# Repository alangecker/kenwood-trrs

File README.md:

# Kenwood TRRS Adapter
A tiny board, which allows using Kenwood headsets on smartphones, including the Push-To-Talk functionality.

## Schematic

## Bill of Materials
| Qty | Ident | Part                     | Notes
|----:|------:|--------------------------|------------
|   1 |    J2 | 2.5mm Jack PJ-211A       |
|   1 |    J3 | 3.5mm Jack PJ-313        | 
|   1 |    J1 | 4-pin 3.5mm Jack Cable   | cut in half
|   1 |    Q1 | AO3400 N-Channel MOSFET  | or BSS138
|   1 |    C1 | 100uF 6.3V RM2 5.0mm Elco
|   1 | R1,R5 | Resistor 100kΩ 0805
|   1 |    R4 | Resistor 2MΩ 0805
|   2 | R2,R3 | Resistor 20Ω 0805
|   1 |       | Heat shrink tube

## License

To the extent possible under law, Andreas Langecker has waived all copyright and related or neighboring rights to kenwood-trrs. This work is published from: Germany

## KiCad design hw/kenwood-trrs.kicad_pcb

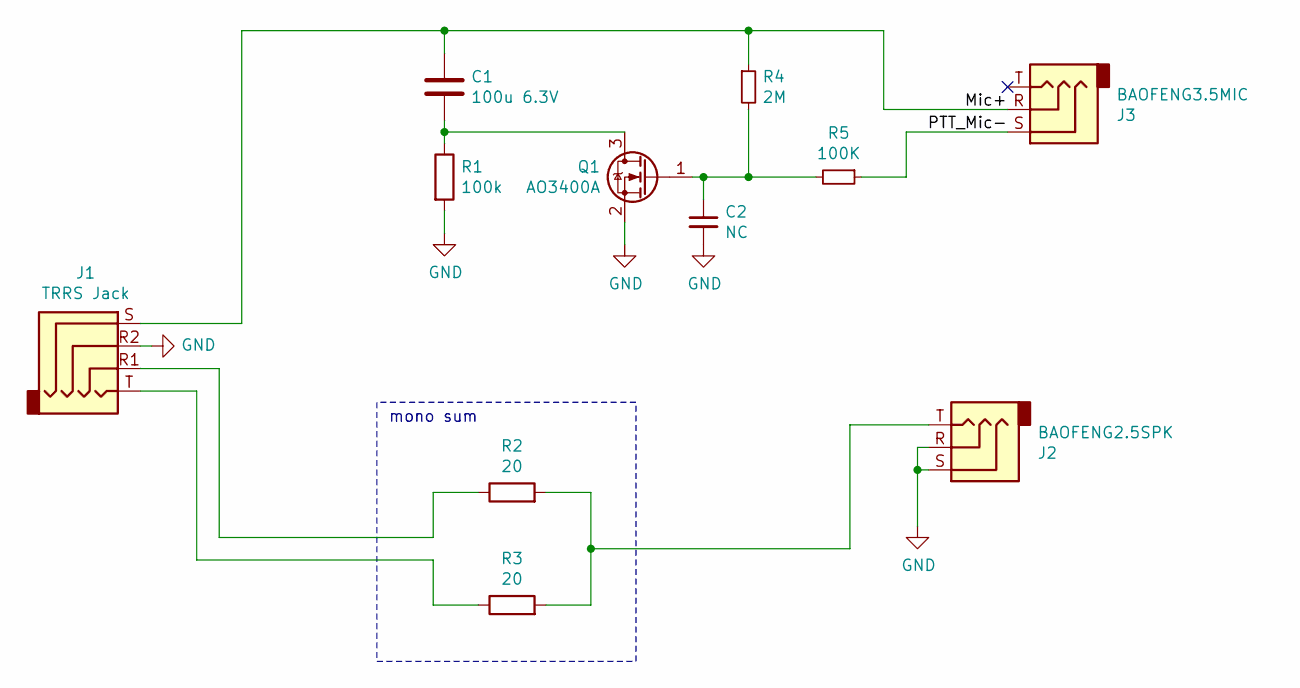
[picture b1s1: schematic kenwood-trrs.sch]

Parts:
C1: 100u 6.3V; CP_Radial_D5.0mm_P2.00mm
C2: NC; C_0805_2012Metric
J1: TRRS Jack; TRRS-Pins
J2: BAOFENG2.5SPK; PJ-211A
J3: BAOFENG3.5MIC; PJ-313-TH
Q1: AO3400A; SOT-23_Handsoldering
R1: 100k; R_0805_2012Metric_Pad1.20x1.40mm_HandSolder
R2, R3: 20; R_0805_2012Metric_Pad1.15x1.40mm_HandSolder
R4: 2M; R_0805_2012Metric_Pad1.20x1.40mm_HandSolder
R5: 100K; R_0805_2012Metric_Pad1.20x1.40mm_HandSolder

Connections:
/Mic+: C1.1, J1.S, J3.R, R4.1
/PTT_Mic-: J3.S, R5.1
GND: C2.2, J1.R2, J2.R, J2.S, Q1.2 (S), R1.2
unnamed: C1.2, Q1.3 (D), R1.1
unnamed: C2.1, Q1.1 (G), R4.2, R5.2
unnamed: J1.R1, R2.1
unnamed: J1.T, R3.1
unnamed: J2.T, R2.2, R3.2

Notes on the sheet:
mono sum

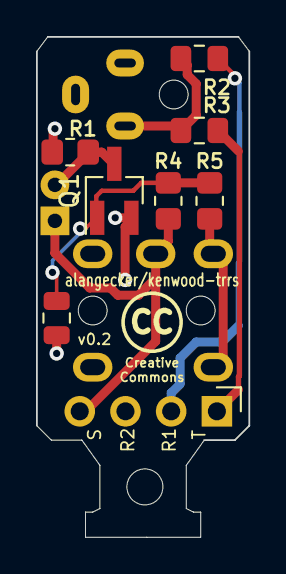
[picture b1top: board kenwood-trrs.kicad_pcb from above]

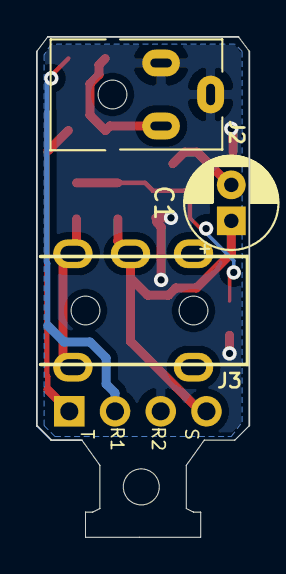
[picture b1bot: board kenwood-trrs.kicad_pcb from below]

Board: 2 copper layers, 11.8 x 27.8 mm, 11 parts (3 on the bottom side), 8 nets.

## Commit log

2020-11-28 fixed jack footprints
2021-05-01 v0.1 gerber files
2021-05-01 new version with different muting mechanism
2021-05-17 version 0.2

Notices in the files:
README.md:
[CC0](http://creativecommons.org/publicdomain/zero/1.0/)
